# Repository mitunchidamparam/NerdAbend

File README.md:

# TwoPointRegulator

For Philip Merkel

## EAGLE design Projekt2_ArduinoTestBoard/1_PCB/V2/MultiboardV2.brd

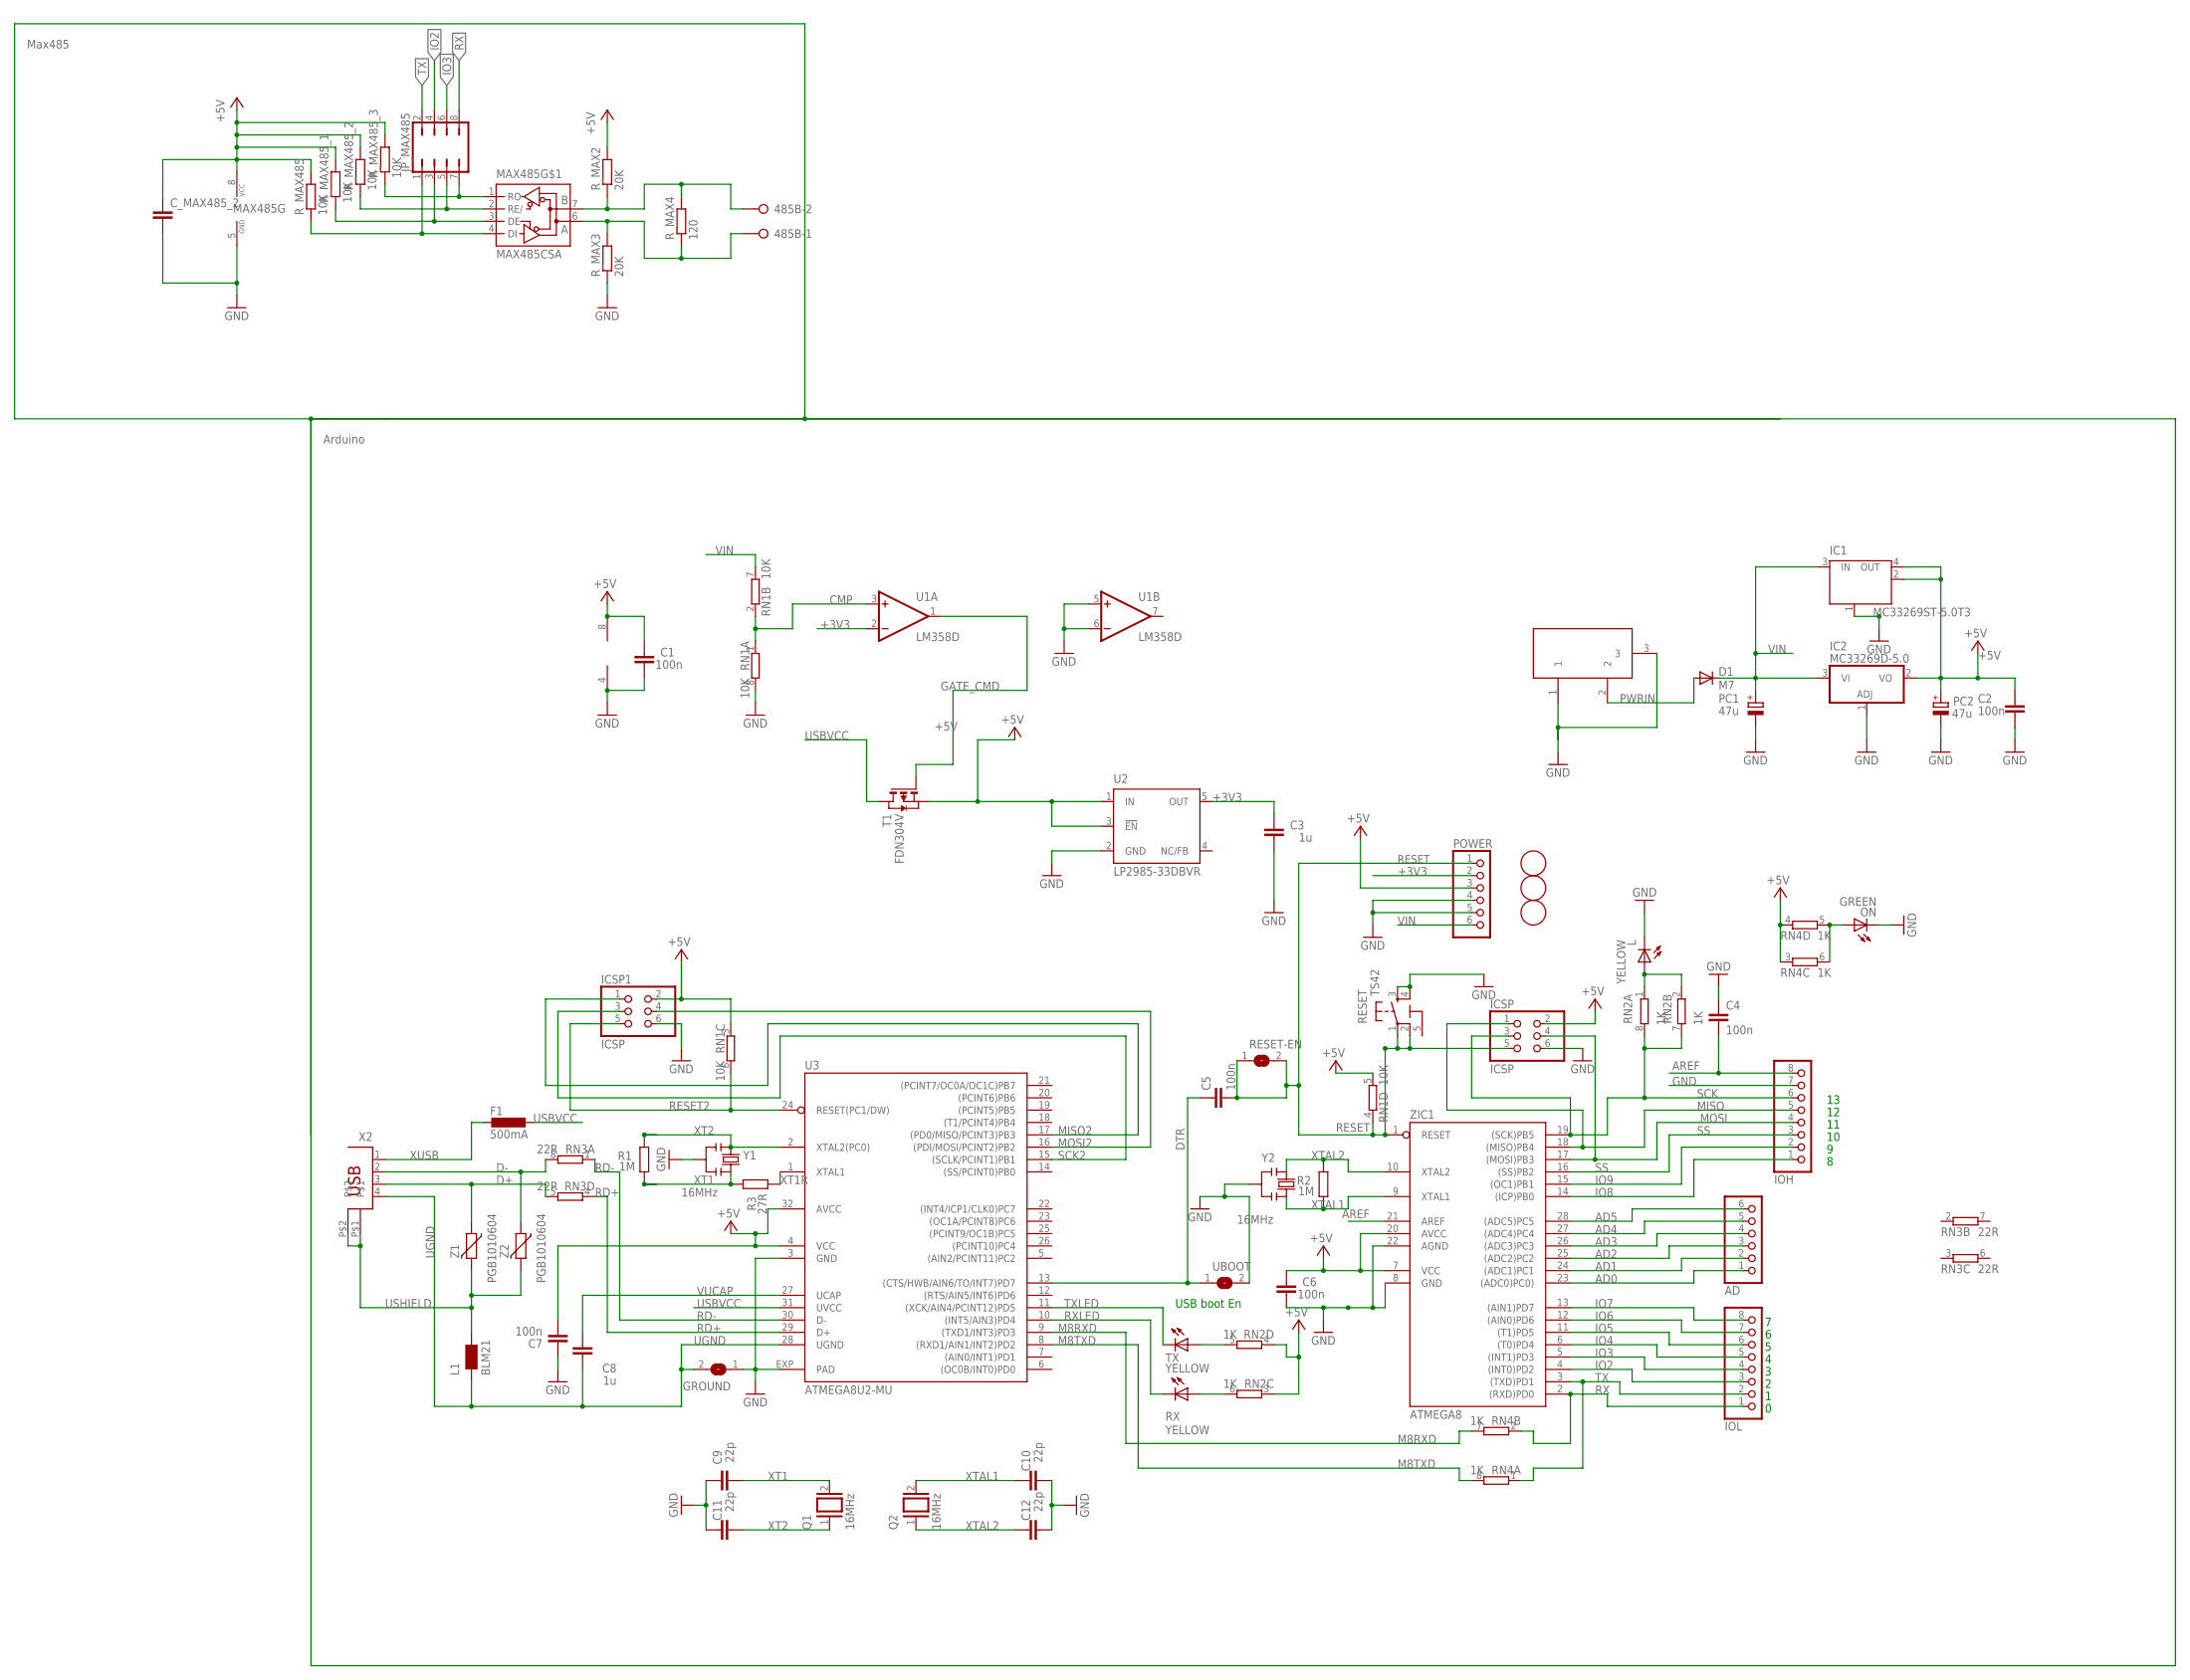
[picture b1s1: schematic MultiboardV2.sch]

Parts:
485B: W237-02P; W237-132
AD: PINHD-1X6; 1X06
C1, C2, C4, C5, C6, C7: 100n; C0603-ROUND
C3, C8: 1u; C0603-ROUND
C9, C10, C11, C12: 22p; C0603-ROUND
C_MAX485_2: C-EUC0402; C0402
D1: M7; SMB
F1: 500mA; L1812
GROUND: SJ
IC1: MC33269ST-5.0T3; SOT223
IC2: MC33269D-5.0; DPACK
ICSP, ICSP1: ICSP; 2X03
IOH: PINHD-1X8; 1X08
IOL: PINHD-1X8; 1X08
JP_MAX485: JP4Q
L: YELLOW; CHIP-LED0805
L1: BLM21; 0805
MAX485: MAX485CSA; SO08
ON: GREEN; CHIP-LED0805
PC1, PC2: 47u; PANASONIC_D
POWER: PINHD-1X6; 1X06
Q1, Q2: 16MHz; QS
R1, R2: 1M; R0603-ROUND
R3: 27R; R0603-ROUND
RESET: TS42
RESET-EN: SJ
RN1: 10K; CAY16
RN2, RN4: 1K; CAY16
RN3: 22R; CAY16
RX: YELLOW; CHIP-LED0805
R_MAX2, R_MAX3: 20K; R0402
R_MAX4: 120; R0402
R_MAX485, R_MAX485_1, R_MAX485_2, R_MAX485_3: 10K; R0402
T1: FDN304V; SOT-23
TX: YELLOW; CHIP-LED0805
U1: LM358D; SO08
U2: LP2985-33DBVR; SOT23-DBV
U3: ATMEGA8U2-MU; QFN32
U$3, U$4, U$6: FIDUCIALMOUNT; FIDUCIA-MOUNT
UBOOT: SJ
X1: DC21MMX; DC-21MM
X2: PN61729
Y1, Y2: 16MHz; RESONATOR
Z1, Z2: PGB1010604; CT/CN0603
ZIC1: ATMEGA8; DIL28-3

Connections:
5-GND: RESET.5 (5-GND)
+3V3: C3.2, POWER.2, U1.2 (-IN), U2.5 (OUT)
+5V: C1.2, C2.2, C6.2, C7.1, C_MAX485_2.1, IC1.2 (OUT), IC1.4 (OUT), IC2.2 (VO), ICSP.2, ICSP1.2, MAX485.8 (VCC), PC2.+, POWER.3, RN1.3 (1), RN1.5 (2), RN2.3 (1), RN2.4 (1), RN4.3 (1), RN4.4 (1), R_MAX2.2, R_MAX485.2, R_MAX485_1.2, R_MAX485_2.2, R_MAX485_3.2, T1.2 (S), U1.8 (V+), U2.1 (IN), U2.3 (!EN), U3.4 (VCC), U3.32 (AVCC), ZIC1.7 (VCC), ZIC1.20 (AVCC)
AD0: AD.1, ZIC1.23 ((ADC0)PC0))
AD1: AD.2, ZIC1.24 ((ADC1)PC1)
AD2: AD.3, ZIC1.25 ((ADC2)PC2)
AD3: AD.4, ZIC1.26 ((ADC3)PC3)
AD4: AD.5, ZIC1.27 ((ADC4)PC4)
AD5: AD.6, ZIC1.28 ((ADC5)PC5)
AREF: C4.2, IOH.8, ZIC1.21 (AREF)
CMP: RN1.1, RN1.2 (1), U1.3 (+IN)
D+: RN3.5 (2), X2.3, Z1.1
D-: RN3.8 (2), X2.2, Z2.1
DTR: C5.1, U3.13 ((CTS/HWB/AIN6/TO/INT7)PD7), UBOOT.1
GATE_CMD: T1.3 (G), U1.1 (OUT)
GND: C1.1, C2.1, C3.1, C4.1, C6.1, C7.2, C9.2, C10.1, C11.2, C12.1, C_MAX485_2.2, GROUND.1, IC1.1 (GND/ADJ), IC2.1 (ADJ), ICSP.6, ICSP1.6, IOH.7, L.C, MAX485.5 (GND), ON.C, PC1.-, PC2.-, POWER.4, POWER.5, RESET.3, RESET.4, RN1.8 (2), R_MAX3.1, U1.4 (V-), U1.5 (+IN), U1.6 (-IN), U2.2 (GND), U3.3 (GND), U3.EXP (PAD), UBOOT.2, X1.1, X1.3, Y1.2, Y2.2, ZIC1.8 (GND), ZIC1.22 (AGND)
IO2: IOL.3, JP_MAX485.4, ZIC1.4 ((INT0)PD2)
IO3: IOL.4, JP_MAX485.6, ZIC1.5 ((INT1)PD3)
IO4: IOL.5, ZIC1.6 ((T0)PD4)
IO5: IOL.6, ZIC1.11 ((T1)PD5)
IO6: IOL.7, ZIC1.12 ((AIN0)PD6)
IO7: IOL.8, ZIC1.13 ((AIN1)PD7)
IO8: IOH.1, ZIC1.14 ((ICP)PB0)
IO9: IOH.2, ZIC1.15 ((OC1)PB1)
M8RXD: RN4.7 (2), U3.9 ((TXD1/INT3)PD3)
M8TXD: RN4.8 (2), U3.8 ((RXD1/AIN1/INT2)PD2)
MISO: ICSP.1, IOH.5, ZIC1.18 ((MISO)PB4)
MISO2: ICSP1.1, U3.17 ((PD0/MISO/PCINT3)PB3)
MOSI: ICSP.4, IOH.4, ZIC1.17 ((MOSI)PB3)
MOSI2: ICSP1.4, U3.16 ((PDI/MOSI/PCINT2)PB2)
unnamed: L.A, RN2.1, RN2.2 (1)
unnamed: ON.A, RN4.5 (2), RN4.6 (2)
unnamed: JP_MAX485.7, MAX485.1 (RO), R_MAX485_3.1
unnamed: JP_MAX485.5, MAX485.2 (RE/), R_MAX485_2.1
unnamed: JP_MAX485.3, MAX485.3 (DE), R_MAX485_1.1
unnamed: JP_MAX485.1, MAX485.4 (DI), R_MAX485.1
unnamed: 485B.2, MAX485.7 (B), R_MAX2.1, R_MAX4.2
unnamed: 485B.1, MAX485.6 (A), R_MAX3.2, R_MAX4.1
unnamed: RN2.6 (2), RX.A
unnamed: RN2.5 (2), TX.A
PWRIN: D1.A, X1.2
RD+: RN3.4 (1), U3.29 (D+)
RD-: RN3.1, U3.30 (D-)
RESET: C5.2, ICSP.5, POWER.1, RESET.1, RESET.2, RESET-EN.1, RESET-EN.2, RN1.4 (1), ZIC1.1 (RESET)
RESET2: ICSP1.5, RN1.6 (2), U3.24 (RESET(PC1/DW))
RX: IOL.1, JP_MAX485.8, RN4.2 (1), ZIC1.2 ((RXD)PD0)
RXLED: RX.C, U3.10 ((INT5/AIN3)PD4)
SCK: ICSP.3, IOH.6, RN2.7 (2), RN2.8 (2), ZIC1.19 ((SCK)PB5)
SCK2: ICSP1.3, U3.15 ((SCLK/PCINT1)PB1)
SS: IOH.3, ZIC1.16 ((SS)PB2)
TX: IOL.2, JP_MAX485.2, RN4.1, ZIC1.3 ((TXD)PD1)
TXLED: TX.C, U3.11 ((XCK/AIN4/PCINT12)PD5)
UGND: C8.2, GROUND.2, L1.1, U3.28 (UGND), X2.4
USBVCC: F1.1, T1.1 (D), U3.31 (UVCC)
USHIELD: L1.2, X2.P$1, X2.P$2, Z1.2, Z2.2
VIN: D1.C, IC1.3 (IN), IC2.3 (VI), PC1.+, POWER.6, RN1.7 (2)
VUCAP: C8.1, U3.27 (UCAP)
XT1: C9.1, Q1.2, R1.1, R3.2, Y1.3
XT1R: R3.1, U3.1 (XTAL1)
XT2: C11.1, Q1.1, R1.2, U3.2 (XTAL2(PC0)), Y1.1
XTAL1: C10.2, Q2.2, R2.1, Y2.3, ZIC1.9 (XTAL1)
XTAL2: C12.2, Q2.1, R2.2, Y2.1, ZIC1.10 (XTAL2)
XUSB: F1.2, X2.1

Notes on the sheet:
USB boot En
Arduino
Max485

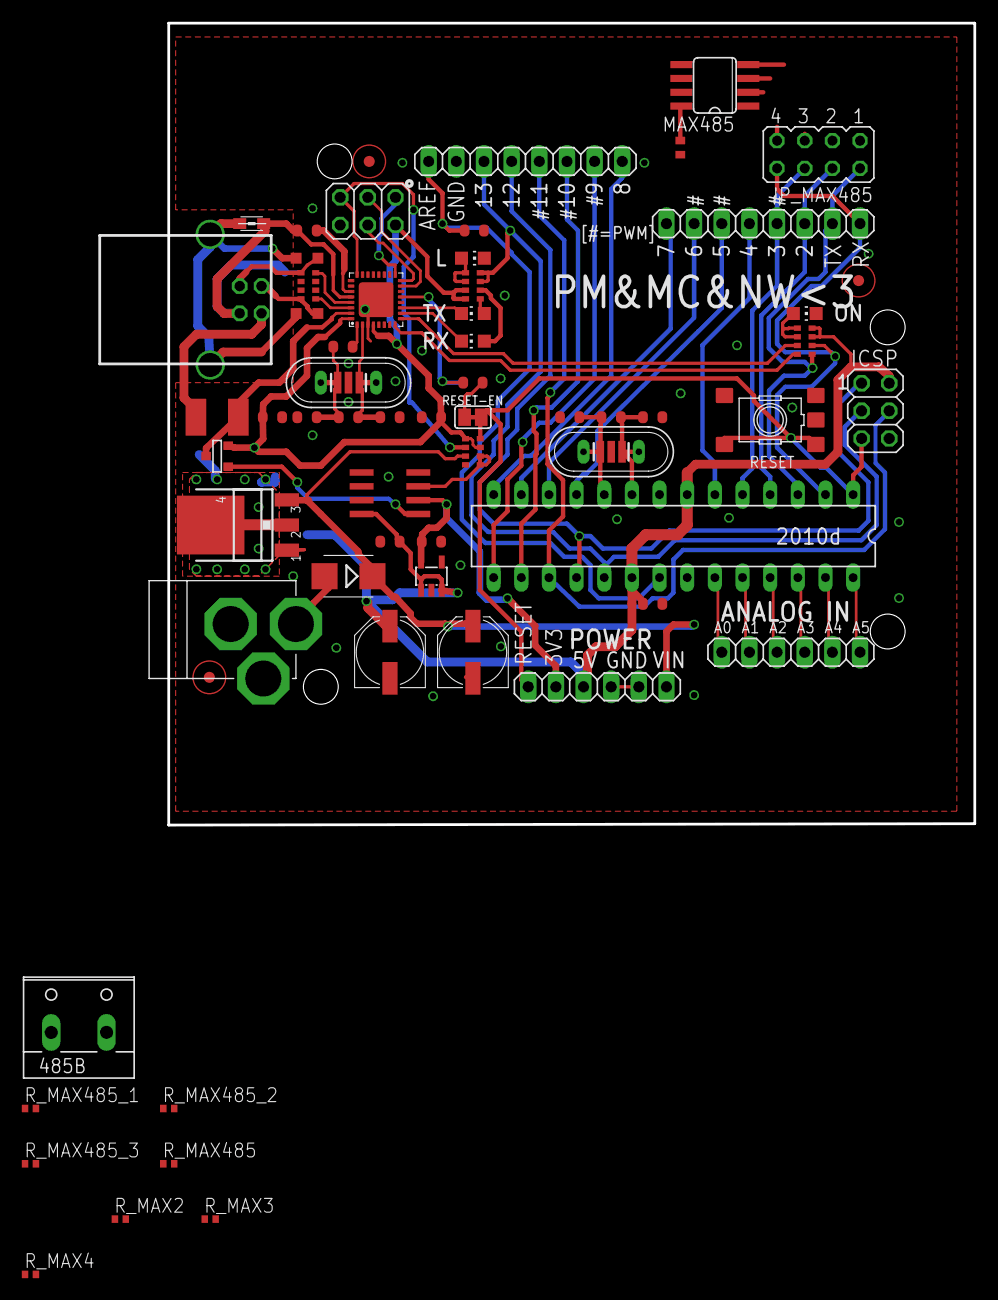
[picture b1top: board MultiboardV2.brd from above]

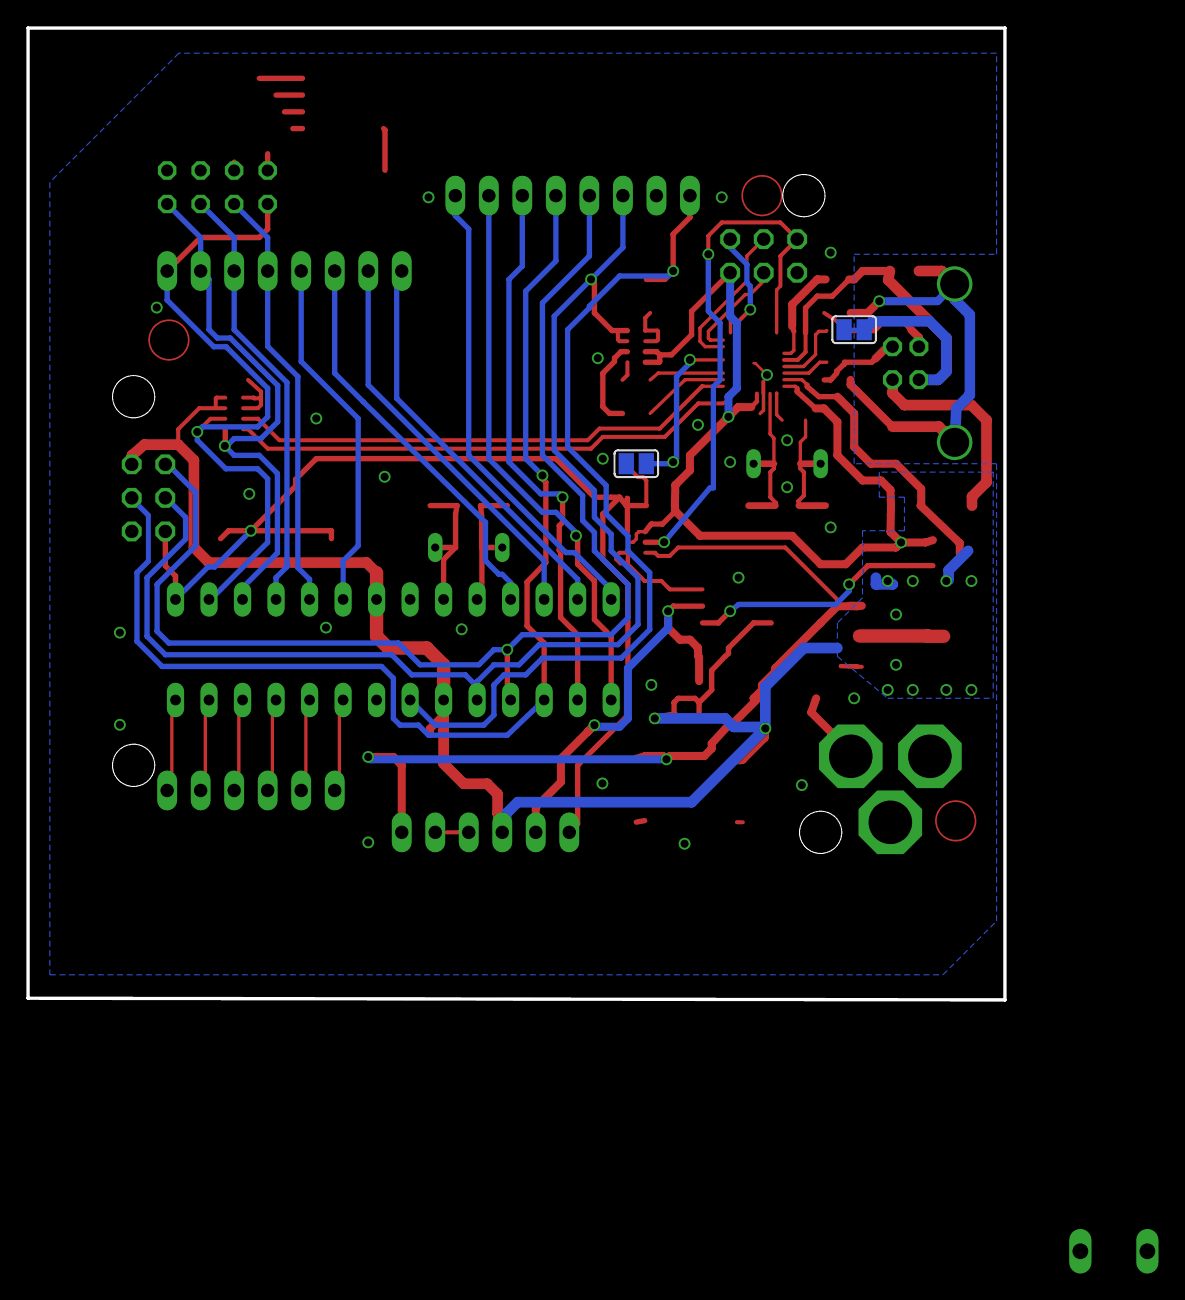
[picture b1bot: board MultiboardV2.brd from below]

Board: 2 copper layers, 74.0 x 73.7 mm, 67 parts (2 on the bottom side), 62 nets.

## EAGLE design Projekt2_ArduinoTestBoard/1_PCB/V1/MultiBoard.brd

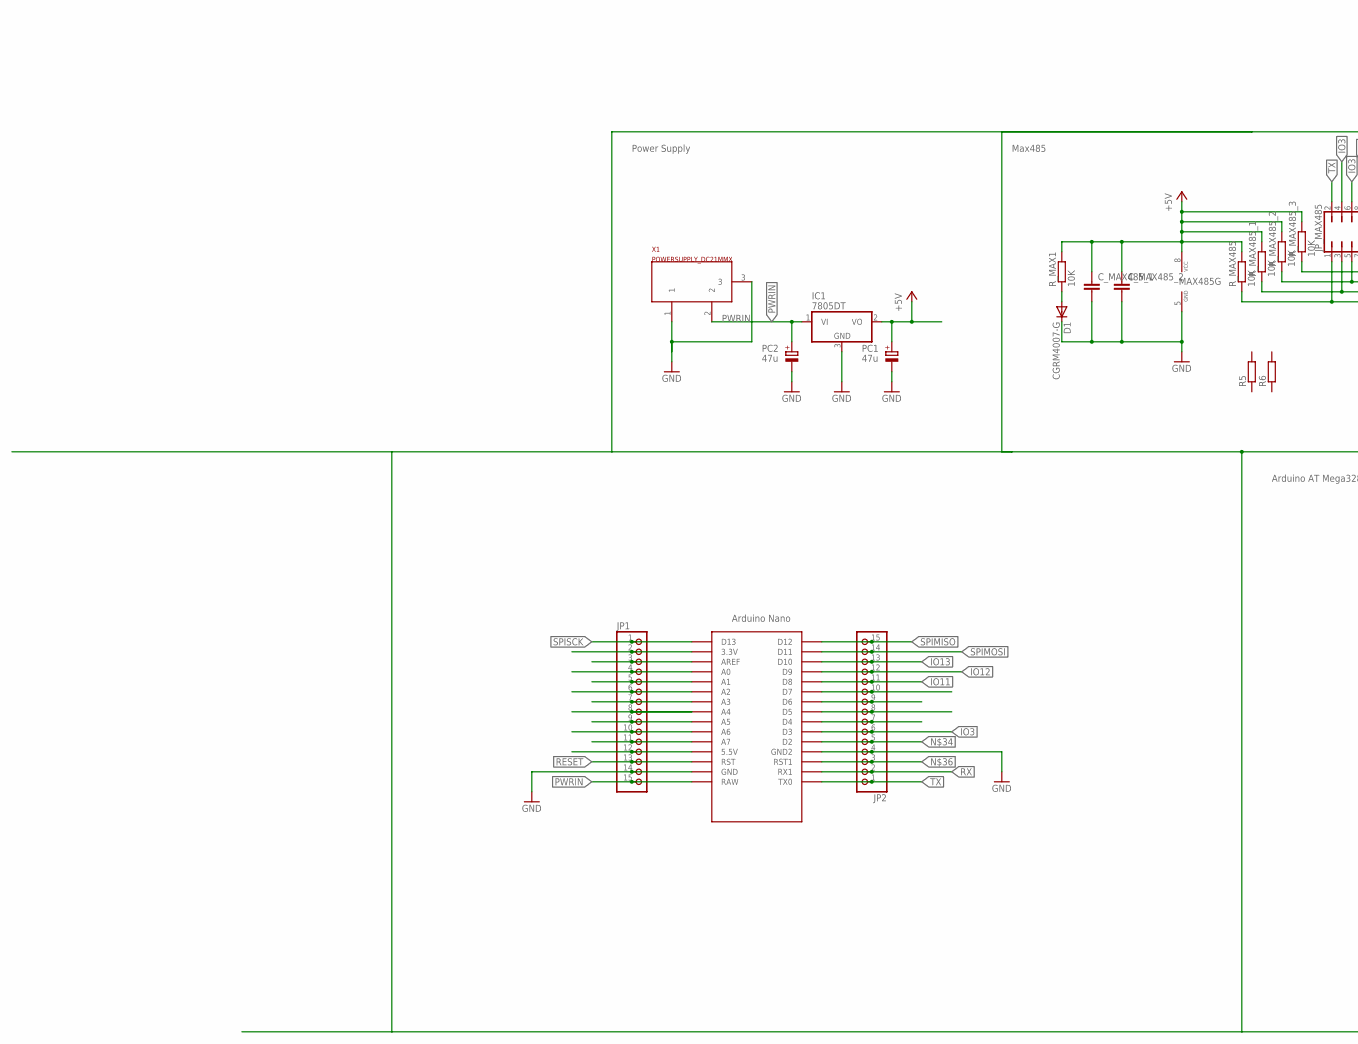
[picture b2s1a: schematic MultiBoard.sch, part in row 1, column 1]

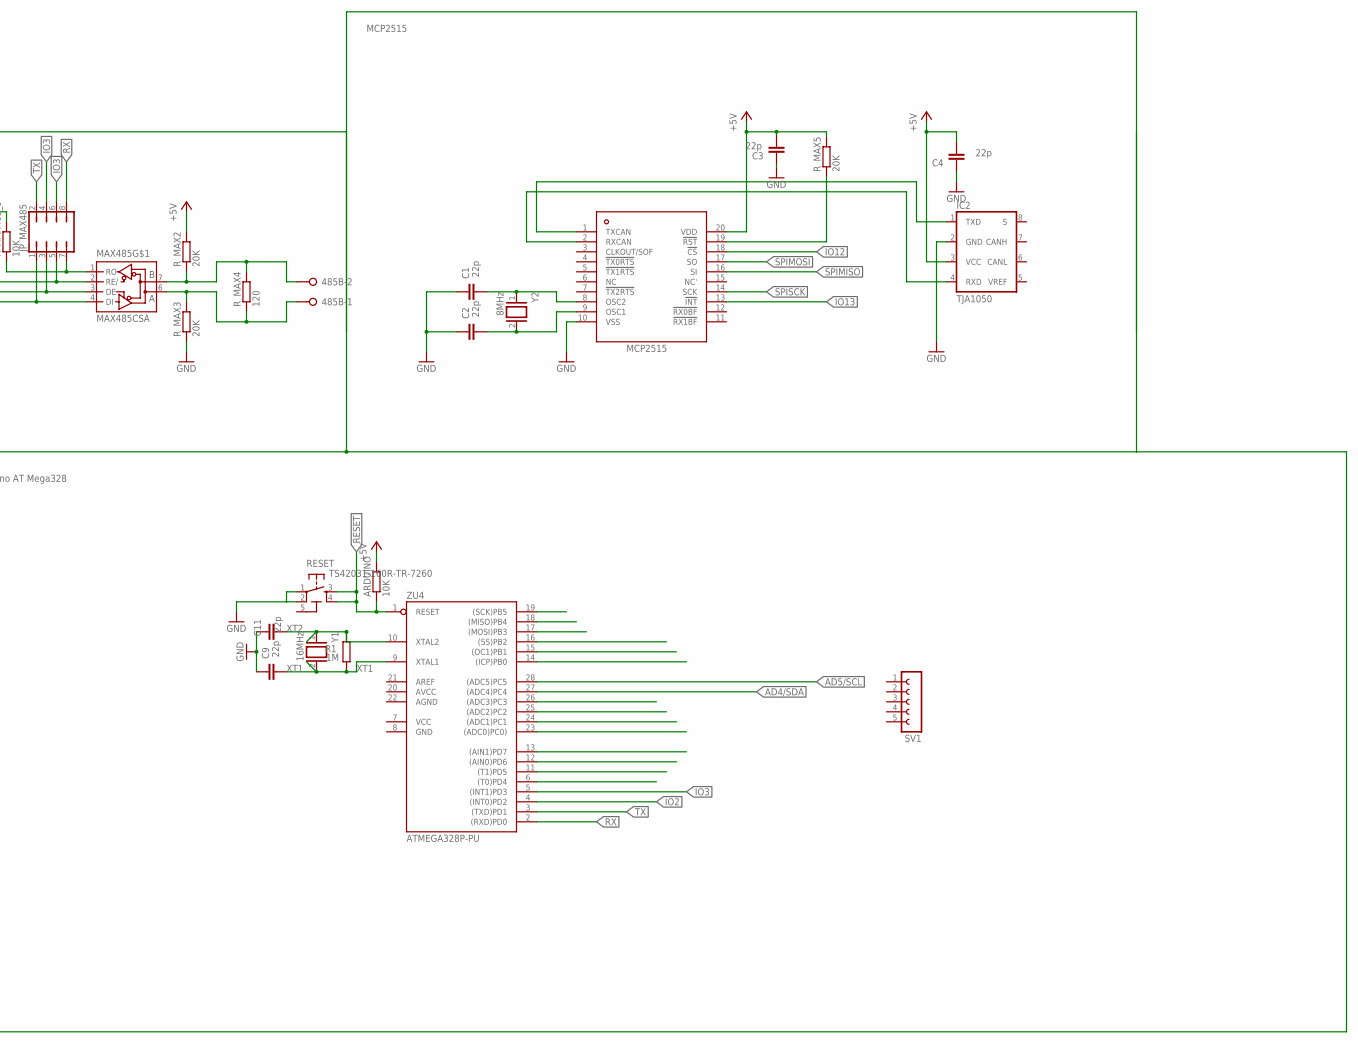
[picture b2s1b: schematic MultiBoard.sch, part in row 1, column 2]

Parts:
485B: W237-02P; W237-132
ARDUINO: 10K; R0402
C1, C2, C3, C4, C9, C11: 22p; C0603-ROUND
C_MAX485_1, C_MAX485_2: C-EUC0402; C0402
D1: CGRM4007-G; SOD-123_MINI-SMA
IC1: 7805DT; TO252
IC2: TJA1050; DIL08
JP1, JP2: PINHD-1X15; 1X15
JP_MAX485: JP4Q
MAX485: MAX485CSA; SO08
PC1, PC2: 47u; PANASONIC_D
R1: 1M; R0603-ROUND
R5, R6: R-EU_M0805; M0805
RESET: TS42031-160R-TR-7260; TS42
R_MAX1, R_MAX485, R_MAX485_1, R_MAX485_2, R_MAX485_3: 10K; R0402
R_MAX2, R_MAX3, R_MAX5: 20K; R0402
R_MAX4: 120; R0402
SV1: FE05-1
U$1: NANO
U$2: MCP2515; TSSOP20
X1: POWERSUPPLY_DC21MMX; POWERSUPPLY_DC-21MM
Y1: 16MHz; QS
Y2: 8MHz; QS
ZU4: ATMEGA328P-PU; DIL28-3

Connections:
5-GND: RESET.5 (5-GND)
+5V: ARDUINO.2, C3.1, C4.1, C_MAX485_1.1, C_MAX485_2.1, IC1.2 (VO), IC2.3 (VCC), MAX485.8 (VCC), PC1.+, R_MAX1.2, R_MAX2.2, R_MAX5.2, R_MAX485.2, R_MAX485_1.2, R_MAX485_2.2, R_MAX485_3.2, U$2.20 (VDD)
AD0: ZU4.23 ((ADC0)PC0))
AD1: ZU4.24 ((ADC1)PC1)
AD2: ZU4.25 ((ADC2)PC2)
AD3: ZU4.26 ((ADC3)PC3)
AD4/SDA: ZU4.27 ((ADC4)PC4)
AD5/SCL: ZU4.28 ((ADC5)PC5)
AGND: ZU4.22 (AGND)
AVCC: ZU4.20 (AVCC)
GND: C1.2, C2.2, C3.2, C4.2, C9.2, C11.2, C_MAX485_1.2, C_MAX485_2.2, D1.C, IC1.3 (GND), IC2.2 (GND), JP1.14, JP2.4, MAX485.5 (GND), PC1.-, PC2.-, RESET.1, RESET.2, R_MAX3.1, U$1.GND, U$1.GND1 (GND2), U$2.10 (VSS), X1.1, X1.3, ZU4.8 (GND)
IO2: ZU4.4 ((INT0)PD2)
IO3: JP2.6, JP_MAX485.4, JP_MAX485.6, U$1.D3, ZU4.5 ((INT1)PD3)
IO4: ZU4.6 ((T0)PD4)
IO5: ZU4.11 ((T1)PD5)
IO6: ZU4.12 ((AIN0)PD6)
IO7: ZU4.13 ((AIN1)PD7)
IO8: ZU4.14 ((ICP)PB0)
IO9: ZU4.15 ((OC1)PB1)
IO11: JP2.11, U$1.D8
IO12: JP2.12, U$1.D9, U$2.18 (!CS)
IO13: JP2.13, U$1.D10, U$2.13 (!INT)
MISO: ZU4.18 ((MISO)PB4)
MOSI: ZU4.17 ((MOSI)PB3)
unnamed: JP_MAX485.7, MAX485.1 (RO), R_MAX485_3.1
unnamed: JP_MAX485.5, MAX485.2 (RE/), R_MAX485_2.1
unnamed: JP_MAX485.3, MAX485.3 (DE), R_MAX485_1.1
unnamed: JP_MAX485.1, MAX485.4 (DI), R_MAX485.1
unnamed: 485B.2, MAX485.7 (B), R_MAX2.1, R_MAX4.2
unnamed: D1.A, R_MAX1.1
unnamed: 485B.1, MAX485.6 (A), R_MAX3.2, R_MAX4.1
unnamed: IC2.1 (TXD), U$2.1 (TXCAN)
unnamed: JP1.2, U$1.3.3V
unnamed: JP1.3, U$1.AREF
unnamed: JP1.4, U$1.A0
unnamed: JP1.5, U$1.A1
unnamed: JP1.6, U$1.A2
unnamed: JP1.7, U$1.A3
unnamed: JP1.8, U$1.A4
unnamed: JP1.9, U$1.A5
unnamed: JP1.10, U$1.A6
unnamed: JP1.11, U$1.A7
unnamed: JP1.12, U$1.5V (5.5V)
unnamed: IC2.4 (RXD), U$2.2 (RXCAN)
unnamed: R_MAX5.1, U$2.19 (!RST)
unnamed: JP2.10, U$1.D7
unnamed: JP2.9, U$1.D6
unnamed: JP2.8, U$1.D5
unnamed: JP2.7, U$1.D4
unnamed: C1.1, U$2.8 (OSC2), Y2.1
unnamed: JP2.5, U$1.D2
unnamed: JP2.3, U$1.RST1
unnamed: C2.1, U$2.9 (OSC1), Y2.2
PWRIN: IC1.1 (VI), JP1.15, PC2.+, U$1.RAW, X1.2
RESET: ARDUINO.1, JP1.13, RESET.3, RESET.4, U$1.RST, ZU4.1 (RESET)
RX: JP2.2, JP_MAX485.8, U$1.RX1, ZU4.2 ((RXD)PD0)
SCK: ZU4.19 ((SCK)PB5)
SPIMISO: JP2.15, U$1.D12, U$2.16 (SI)
SPIMOSI: JP2.14, U$1.D11, U$2.17 (SO)
SPISCK: JP1.1, U$1.D13, U$2.14 (SCK)
SS: ZU4.16 ((SS)PB2)
TX: JP2.1, JP_MAX485.2, U$1.TX0, ZU4.3 ((TXD)PD1)
VCC: ZU4.7 (VCC)
XT1: C9.1, R1.1, Y1.2, ZU4.9 (XTAL1)
XT2: C11.1, R1.2, Y1.1, ZU4.10 (XTAL2)

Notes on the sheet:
Max485
Arduino AT Mega328
Power Supply
MCP2515

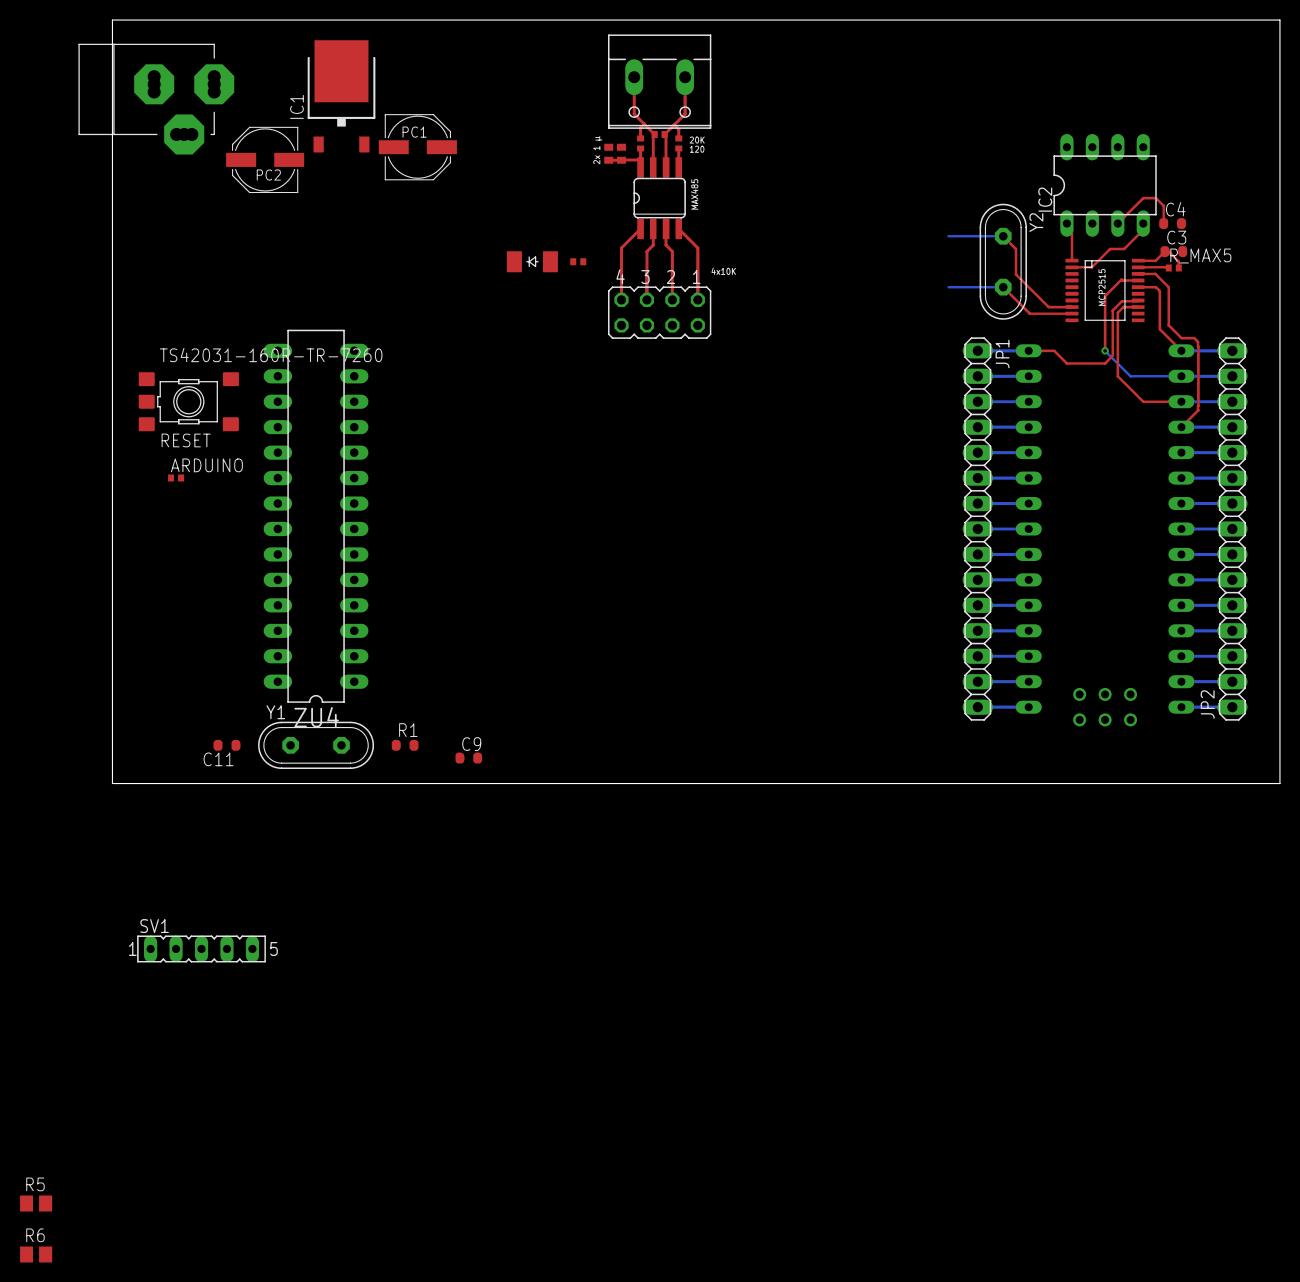
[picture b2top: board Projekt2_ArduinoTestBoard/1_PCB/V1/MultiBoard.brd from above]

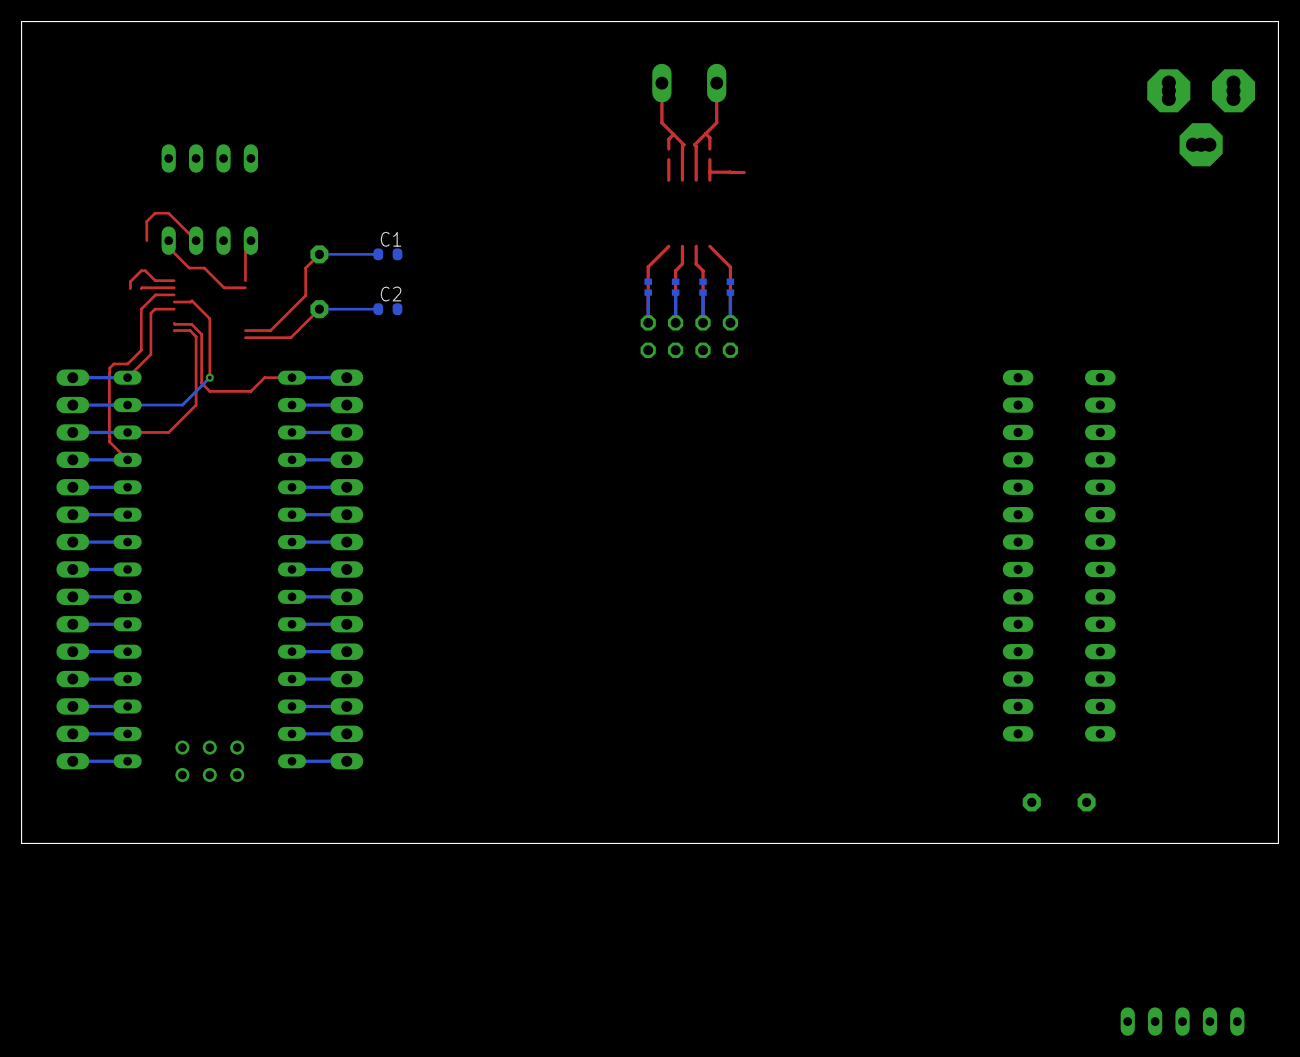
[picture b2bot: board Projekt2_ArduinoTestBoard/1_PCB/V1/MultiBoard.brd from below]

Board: 2 copper layers, 116.5 x 76.2 mm, 39 parts (6 on the bottom side), 44 nets.

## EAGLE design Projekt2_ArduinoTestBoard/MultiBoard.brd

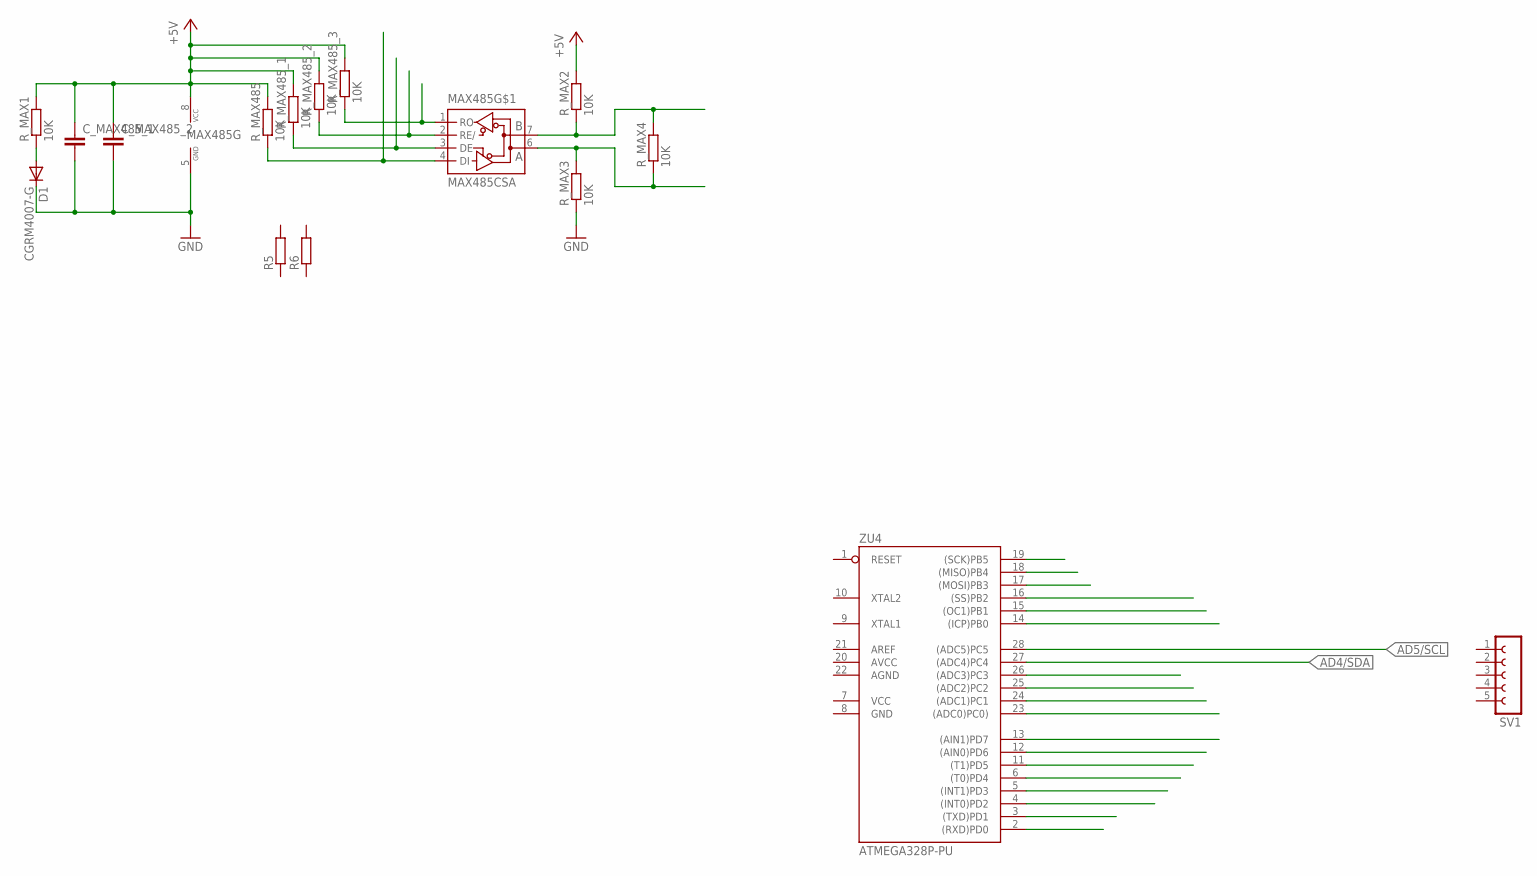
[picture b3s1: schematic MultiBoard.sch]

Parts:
C_MAX485_1, C_MAX485_2: C-EUC0805; C0805
D1: CGRM4007-G; SOD-123_MINI-SMA
MAX485: MAX485CSA; SO08
R5, R6: R-EU_M0805; M0805
R_MAX1, R_MAX2, R_MAX3, R_MAX4, R_MAX485, R_MAX485_1, R_MAX485_2, R_MAX485_3: 10K; R0402
SV1: FE05-1
ZU4: ATMEGA328P-PU; DIL28-3

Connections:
+5V: C_MAX485_1.1, C_MAX485_2.1, MAX485.8 (VCC), R_MAX1.2, R_MAX2.2, R_MAX485.2, R_MAX485_1.2, R_MAX485_2.2, R_MAX485_3.2
AD0: ZU4.23 ((ADC0)PC0))
AD1: ZU4.24 ((ADC1)PC1)
AD2: ZU4.25 ((ADC2)PC2)
AD3: ZU4.26 ((ADC3)PC3)
AD4/SDA: ZU4.27 ((ADC4)PC4)
AD5/SCL: ZU4.28 ((ADC5)PC5)
AGND: ZU4.22 (AGND)
AVCC: ZU4.20 (AVCC)
GND: C_MAX485_1.2, C_MAX485_2.2, D1.C, MAX485.5 (GND), R_MAX3.1, ZU4.8 (GND)
IO0: ZU4.2 ((RXD)PD0)
IO1: ZU4.3 ((TXD)PD1)
IO2: ZU4.4 ((INT0)PD2)
IO3: ZU4.5 ((INT1)PD3)
IO4: ZU4.6 ((T0)PD4)
IO5: ZU4.11 ((T1)PD5)
IO6: ZU4.12 ((AIN0)PD6)
IO7: ZU4.13 ((AIN1)PD7)
IO8: ZU4.14 ((ICP)PB0)
IO9: ZU4.15 ((OC1)PB1)
MISO: ZU4.18 ((MISO)PB4)
MOSI: ZU4.17 ((MOSI)PB3)
unnamed: MAX485.1 (RO), R_MAX485_3.1
unnamed: MAX485.2 (RE/), R_MAX485_2.1
unnamed: MAX485.3 (DE), R_MAX485_1.1
unnamed: MAX485.4 (DI), R_MAX485.1
unnamed: MAX485.7 (B), R_MAX2.1, R_MAX4.2
unnamed: D1.A, R_MAX1.1
unnamed: MAX485.6 (A), R_MAX3.2, R_MAX4.1
SCK: ZU4.19 ((SCK)PB5)
SS: ZU4.16 ((SS)PB2)
VCC: ZU4.7 (VCC)

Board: 2 copper layers, 16 parts (0 on the bottom side), 9 nets, no tracks yet.

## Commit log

2018-12-14 Cleanup Repository
2018-12-14 Calibration of Datasheet in Matlab
2018-12-24 Setup
2018-12-24 Addition of RS-485 Component
2018-12-24 Uno Reference Design
2018-12-24 Adafruit-Si7021-PCB_Temp_Humidity_Reference
2018-12-24 max485
2018-12-24 git merge
2018-12-25 Update PCB
2018-12-25 added mcp 2515
2018-12-28 PCB Update
2019-01-02 V2 PCB Setup
2019-01-02 Multiboard V2
2019-01-04 Added SD Card Holder
2019-01-06 Added RGB LEDs
2019-02-01 Gesture Sensor
2019-02-02 Test
2019-02-15 eInkDisplayLib
2019-02-21 2,9 Inch Dispaly
2019-03-07 4.2 inch display
2019-04-03 SD Card + Ws2812
2019-10-20 Nicolas
    Eink 1,54 inch Update
2019-11-10 Nicolas Update
